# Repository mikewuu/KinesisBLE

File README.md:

# Wireless Kinesis Advantage BLE (Bluetooth Low Energy)

Turns the [Kinesis Advantage Keyboard](https://www.kinesis-ergo.com/shop/advantage2/) keyboard into a wireless BLE keyboard with a few extra features. Built with Adafruit's nRF52 Feather Arduino boards.

For instructions, see the **[wiki](https://github.com/sysdevmike/KinesisBLE/wiki)**. For more details on the build check out the **[project](https://hackaday.io/project/161578-wireless-ble-kinesis-advantage-custom-controller)**.

## Many thanks to

- [Yin Zhong](https://summivox.wordpress.com/2016/06/03/keyboard-matrix-scanning-and-debouncing/) - Explains a better way to handle debouncing.
- [Stapelberg](https://michael.stapelberg.ch/posts/2018-04-17-kinx-keyboard-controller/) - Double mention as I ported his debouncing used in his KinX controller to Matt's firmware.
- [Matt Vilim](https://github.com/mattvilim/FeatherCtrl) - New firmware is a fork of his FeatherCtrl project.
- [Adafruit](https://www.adafruit.com/product/3406) - Great documentation, libs and support.
- [afriggeri](https://github.com/afriggeri/kb) - The original firmware borrowed heavily from his [Blanck Keyboard](https://medium.com/@friggeri/the-blanck-keyboard-24afe12e81a) project.
- [Stapelberg](https://michael.stapelberg.de/posts/2013-03-21-kinesis_custom_controller/) - Michael Stapelberg's custom controller inspired this project. His PCB routing was inspirational.
- [Humble Hacker](http://humblehacker.com/blog/20100720/hacking-the-kinesis-contoured-keyboard/) - Detailed write-up helped me understand the keyboard matrix.
- [PCBgogo](http://www.pcbgogo.com) - All the boards were made by these guys. Fast turn-around.

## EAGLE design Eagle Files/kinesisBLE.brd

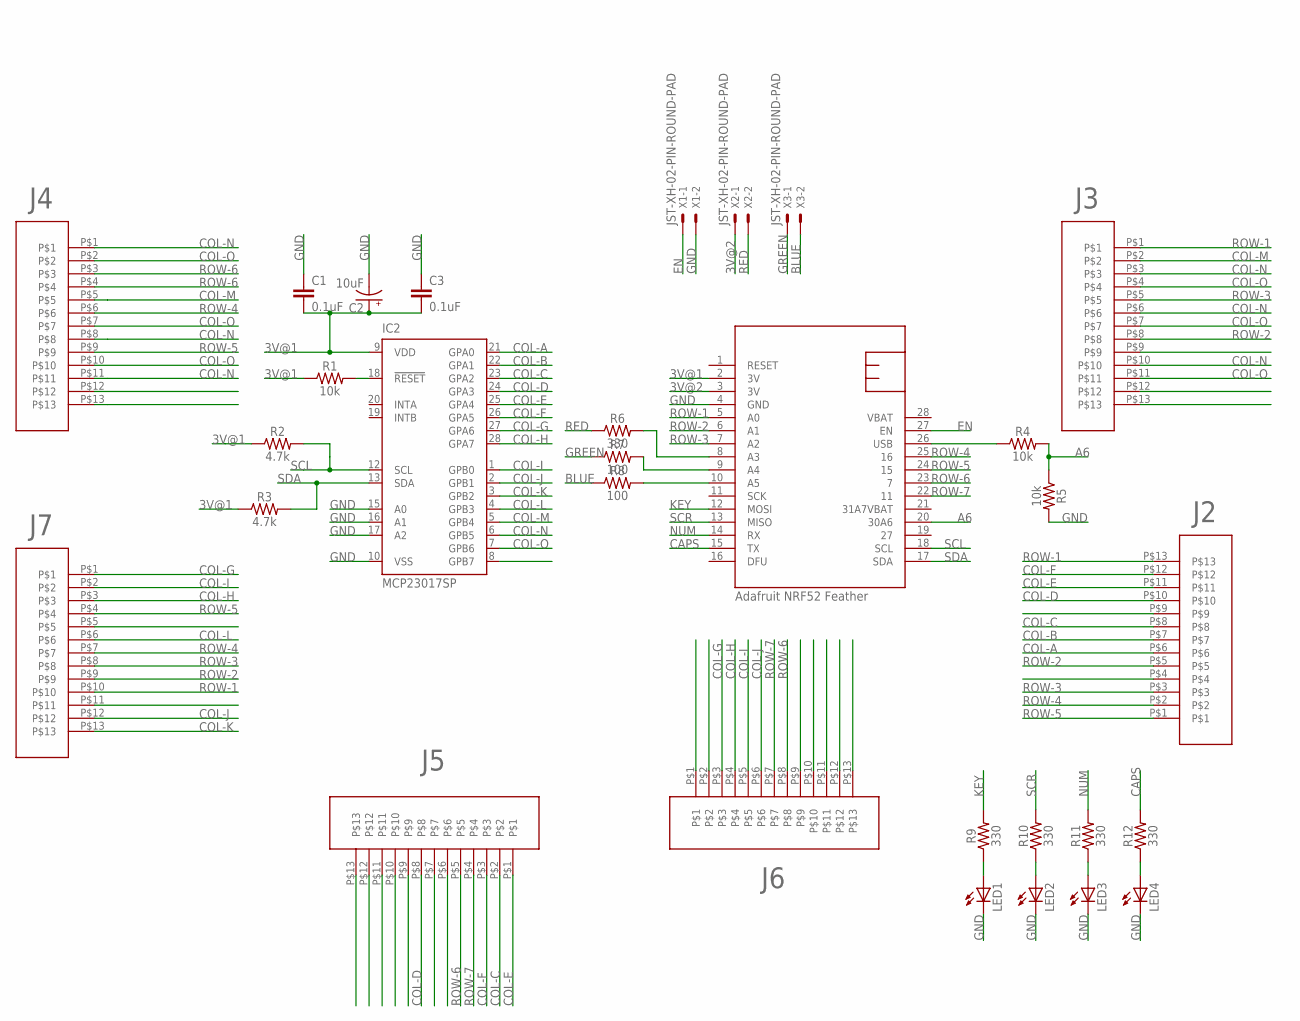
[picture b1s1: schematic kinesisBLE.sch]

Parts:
C1, C3: 0.1uF; CAP-PTH-SMALL-KIT
C2: 10uF; CPOL-RADIAL-2.5MM-5MM
IC2: MCP23017SP; DIL28-3
LED1, LED2, LED3, LED4: LED3MM
R1, R4, R5: 10k; AXIAL-0.3
R2, R3: 4.7k; AXIAL-0.3
R6, R9, R10, R11, R12: 330; AXIAL-0.3
R7, R8: 100; AXIAL-0.3
U$1: NRF52FEATHER
U$2, U$3, U$4, U$5, U$6, U$7: TOPLINKS_STAPELBERG
X1, X2, X3: JST-XH-02-PIN-ROUND-PAD; JST-XH-02-PACKAGE-ROUND-PAD

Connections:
3V@1: C1.2, C2.1 (+), C3.2, IC2.9 (VDD), R1.P$1 (1), R2.P$1 (1), R3.P$1 (1), U$1.2 (3V)
3V@2: U$1.3 (3V), X2.1
A6: R4.P$2 (2), R5.P$1 (1), U$1.20 (30A6)
BLUE: R8.P$1 (1), X3.2
CAPS: R12.P$2 (2), U$1.15 (TX)
COL-A: IC2.21 (GPA0), U$5.P$6
COL-B: IC2.22 (GPA1), U$5.P$7
COL-C: IC2.23 (GPA2), U$5.P$8, U$6.P$2
COL-D: IC2.24 (GPA3), U$5.P$10, U$6.P$8
COL-E: IC2.25 (GPA4), U$5.P$11, U$6.P$1
COL-F: IC2.26 (GPA5), U$5.P$12, U$6.P$3
COL-G: IC2.27 (GPA6), U$4.P$1, U$7.P$3
COL-H: IC2.28 (GPA7), U$4.P$3, U$7.P$4
COL-I: IC2.1 (GPB0), U$4.P$2, U$7.P$5
COL-J: IC2.2 (GPB1), U$4.P$12, U$7.P$6
COL-K: IC2.3 (GPB2), U$4.P$13
COL-L: IC2.4 (GPB3), U$4.P$6
COL-M: IC2.5 (GPB4), U$2.P$5, U$3.P$2
COL-N: IC2.6 (GPB5), U$2.P$1, U$2.P$8, U$2.P$11, U$3.P$3, U$3.P$6, U$3.P$10
COL-O: IC2.7 (GPB6), U$2.P$2, U$2.P$7, U$2.P$10, U$3.P$4, U$3.P$7, U$3.P$11
EN: U$1.27 (EN), X1.1
GND: C1.1, C2.2 (-), C3.1, IC2.10 (VSS), IC2.15 (A0), IC2.16 (A1), IC2.17 (A2), LED1.K (C), LED2.K (C), LED3.K (C), LED4.K (C), R5.P$2 (2), U$1.4 (GND), X1.2
GREEN: R7.P$1 (1), X3.1
KEY: R9.P$2 (2), U$1.12 (MOSI)
unnamed: LED1.A, R9.P$1 (1)
unnamed: IC2.18 (!RESET), R1.P$2 (2)
unnamed: R4.P$1 (1), U$1.26 (USB)
unnamed: R6.P$2 (2), U$1.8 (A3)
unnamed: R7.P$2 (2), U$1.9 (A4)
unnamed: R8.P$2 (2), U$1.10 (A5)
unnamed: LED2.A, R10.P$1 (1)
unnamed: LED3.A, R11.P$1 (1)
unnamed: LED4.A, R12.P$1 (1)
NUM: R11.P$2 (2), U$1.14 (RX)
RED: R6.P$1 (1), X2.2
ROW-1: U$1.5 (A0), U$3.P$1, U$4.P$10, U$5.P$13
ROW-2: U$1.6 (A1), U$3.P$8, U$4.P$9, U$5.P$5
ROW-3: U$1.7 (A2), U$3.P$5, U$4.P$8, U$5.P$3
ROW-4: U$1.25 (16), U$2.P$6, U$4.P$7, U$5.P$2
ROW-5: U$1.24 (15), U$2.P$9, U$4.P$4, U$5.P$1
ROW-6: U$1.23 (7), U$2.P$3, U$2.P$4, U$6.P$5, U$7.P$8
ROW-7: U$1.22 (11), U$6.P$4, U$7.P$7
SCL: IC2.12 (SCL), R2.P$2 (2), U$1.18 (SCL)
SCR: R10.P$2 (2), U$1.13 (MISO)
SDA: IC2.13 (SDA), R3.P$2 (2), U$1.17 (SDA)
VBAT: U$1.28 (VBAT)

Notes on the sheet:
Adafruit NRF52 Feather

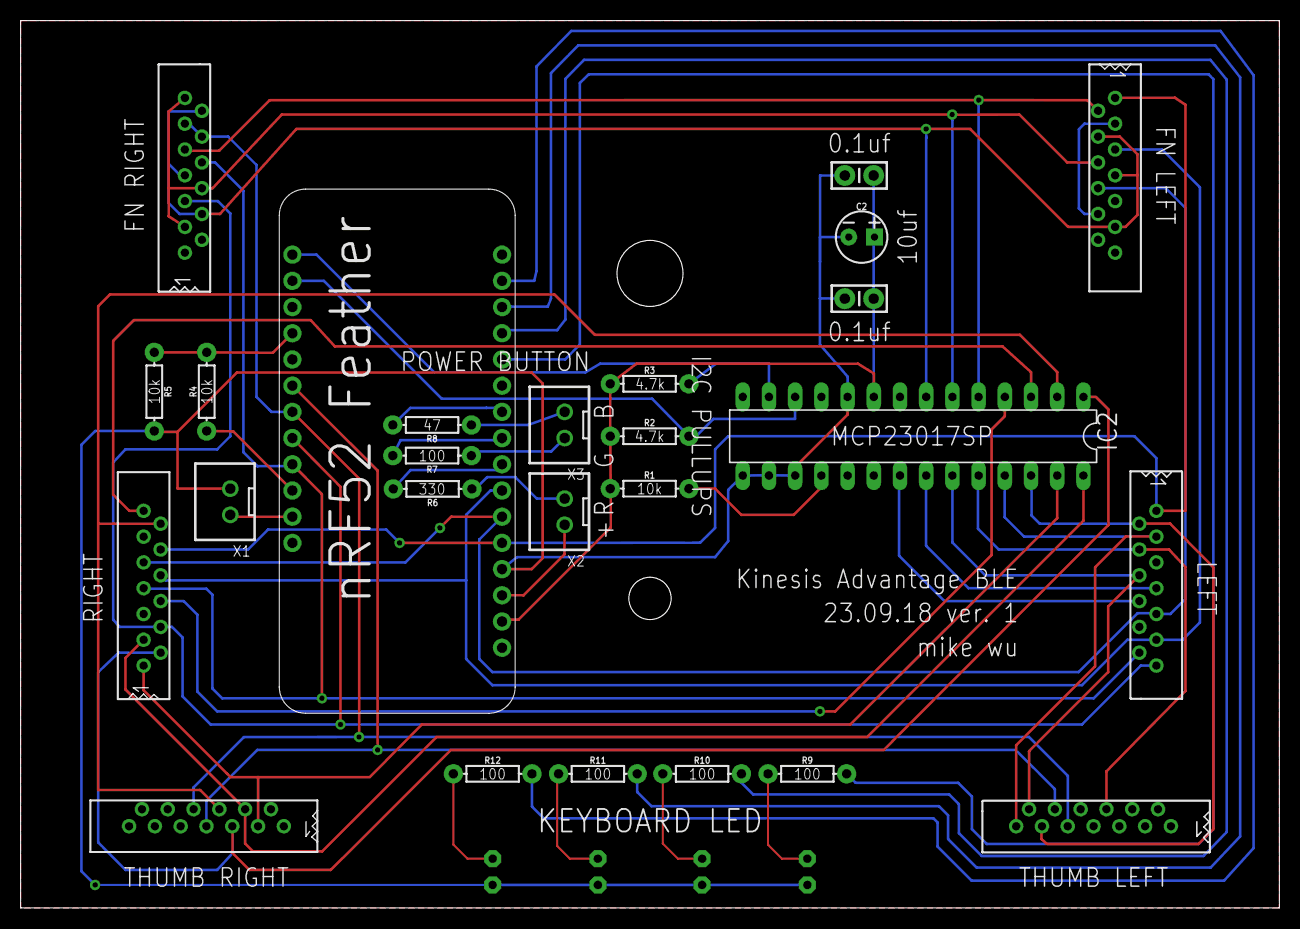
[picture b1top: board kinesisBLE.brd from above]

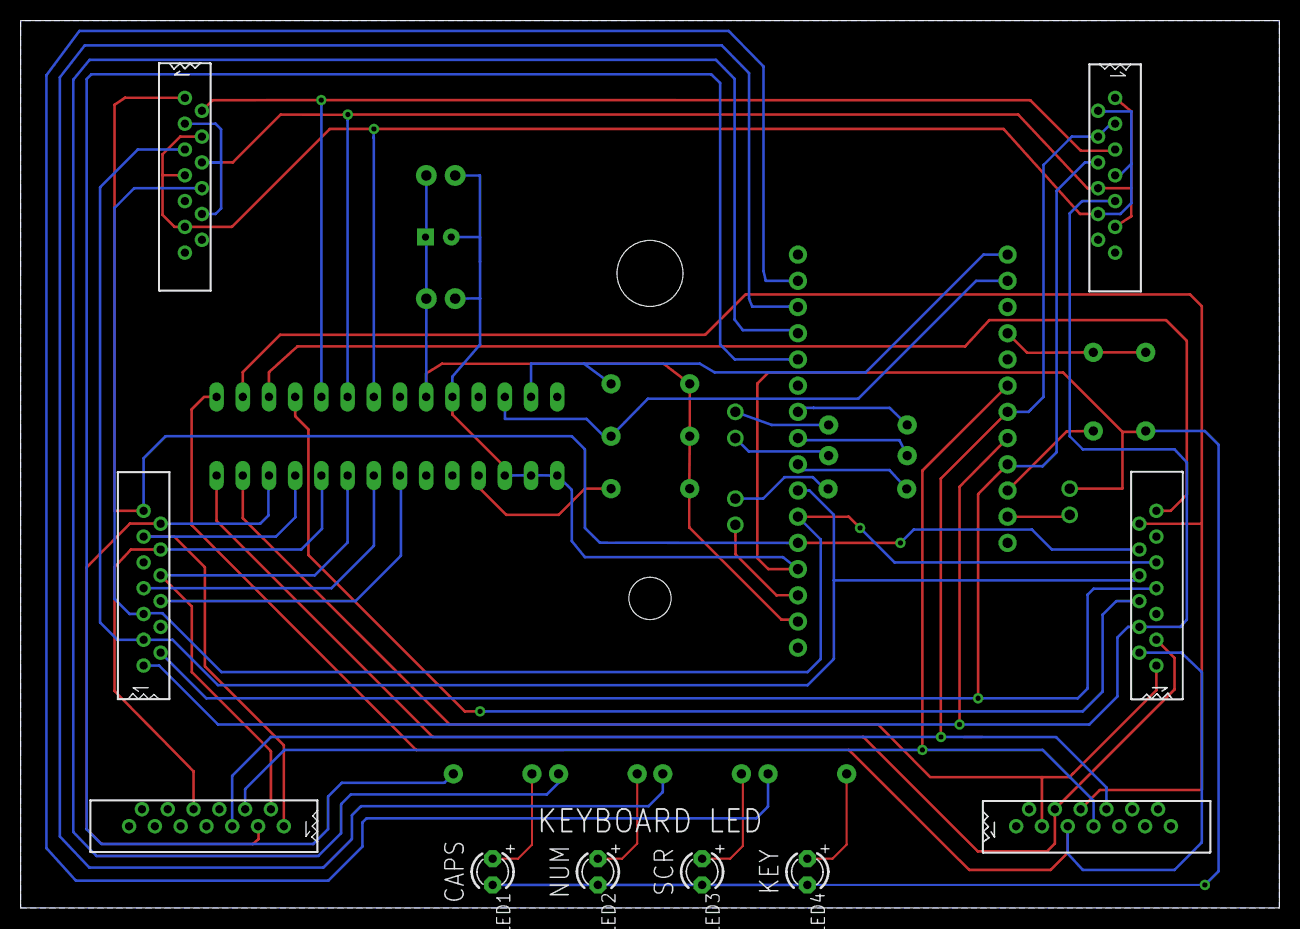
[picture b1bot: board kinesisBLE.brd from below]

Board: 2 copper layers, 122.0 x 86.0 mm, 30 parts (7 on the bottom side), 45 nets.

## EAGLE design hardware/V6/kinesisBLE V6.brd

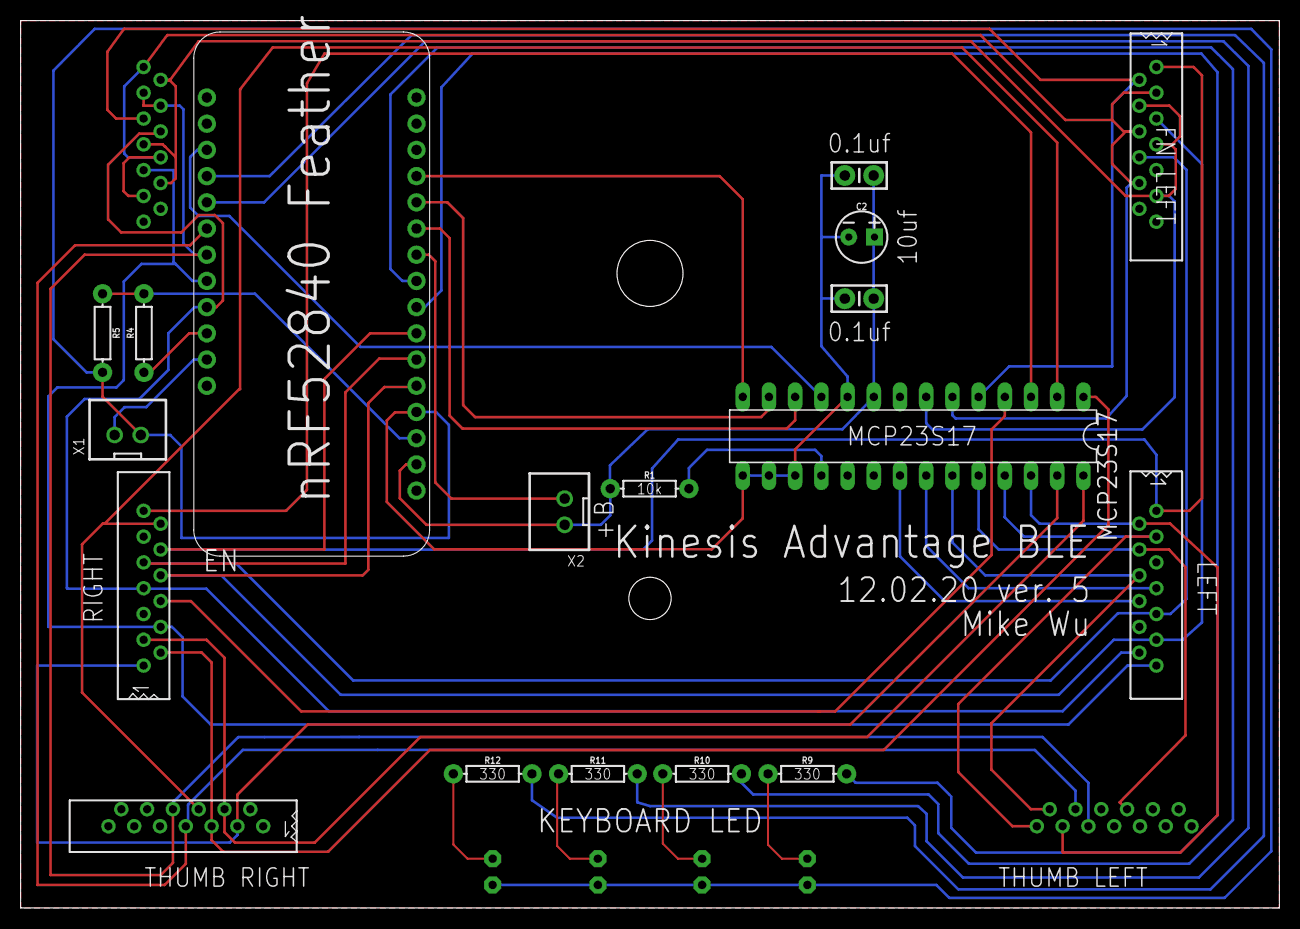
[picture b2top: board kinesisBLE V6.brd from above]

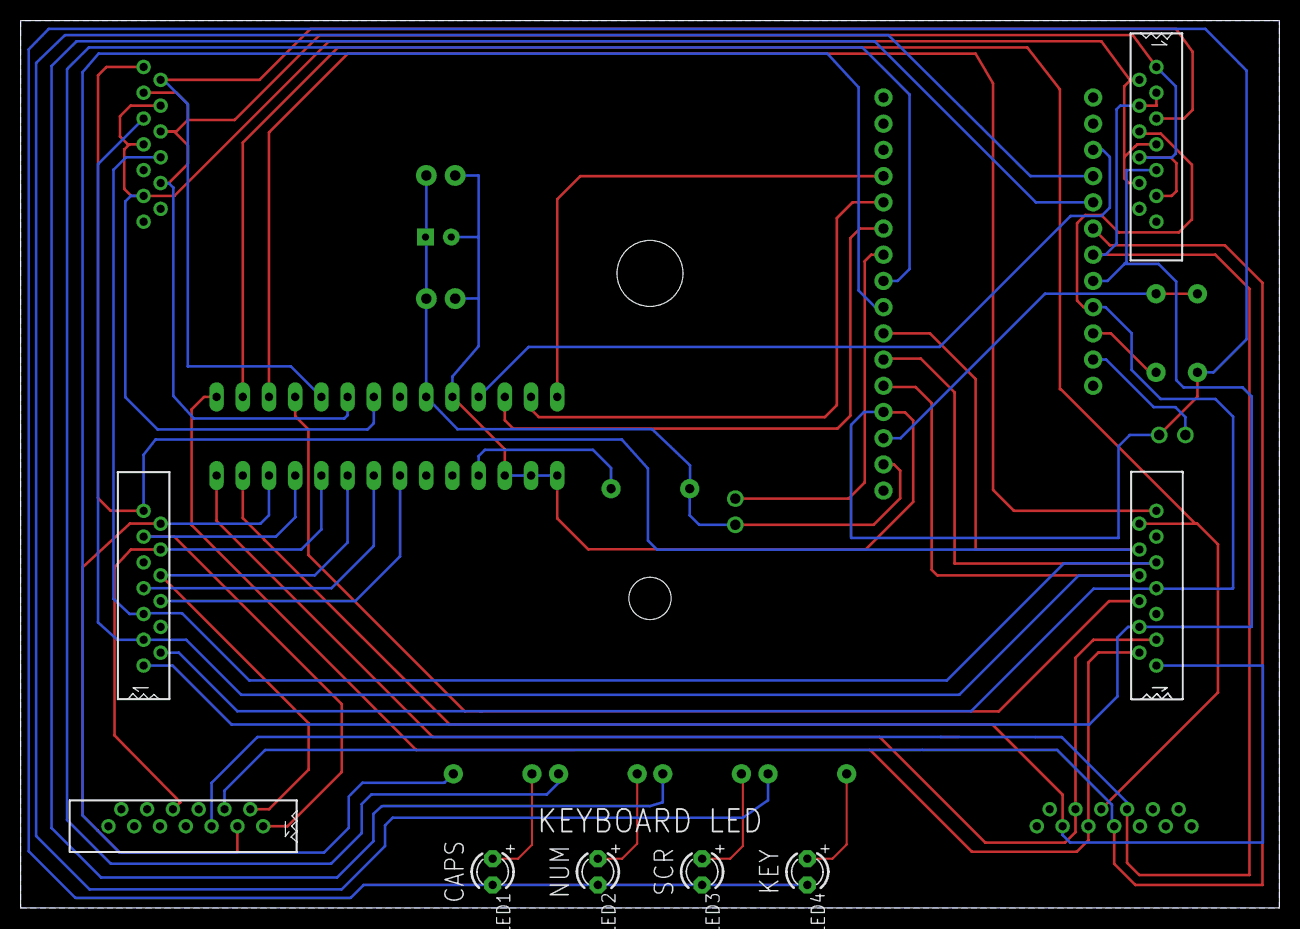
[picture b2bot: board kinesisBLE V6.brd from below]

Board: 2 copper layers, 122.0 x 86.0 mm, 24 parts (7 on the bottom side), 41 nets.

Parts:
C1, C3: 0.1uF; CAP-PTH-SMALL-KIT
C2: 10uF; CPOL-RADIAL-2.5MM-5MM
LED1, LED2, LED3, LED4: LED3MM
MCP23S17: MCP23S17SP; DIL28-3
R1, R4, R5: 10k; AXIAL-0.3
R9, R10, R11, R12: 330; AXIAL-0.3
U$1: NRF52FEATHER
U$2, U$3, U$4, U$5, U$6, U$7: TOPLINKS_STAPELBERG
X1, X2: JST-XH-02-PIN-ROUND-PAD; JST-XH-02-PACKAGE-ROUND-PAD

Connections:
3V@1: C1.2, C2.1, C3.2, MCP23S17.9, R1.P$1, U$1.2, X2.1
AREF: R4.P$2, R5.P$1, U$1.3
BLUE: U$1.10, X2.2
CAPS: R9.P$2, U$1.8
COL-A: MCP23S17.21, U$5.P$6
COL-B: MCP23S17.22, U$5.P$7
COL-C: MCP23S17.23, U$5.P$8, U$6.P$2
COL-D: MCP23S17.24, U$5.P$10, U$6.P$8
COL-E: MCP23S17.25, U$5.P$11, U$6.P$1
COL-F: MCP23S17.26, U$5.P$12, U$6.P$3
COL-G: MCP23S17.27, U$4.P$1, U$7.P$3
COL-H: MCP23S17.28, U$4.P$3, U$7.P$4
COL-I: MCP23S17.1, U$4.P$2, U$7.P$5
COL-J: MCP23S17.2, U$4.P$12, U$7.P$6
COL-K: MCP23S17.3, U$4.P$13
COL-L: MCP23S17.4, U$4.P$6
COL-M: MCP23S17.5, U$2.P$5, U$3.P$2
COL-N: MCP23S17.6, U$2.P$1, U$2.P$8, U$2.P$11, U$3.P$3, U$3.P$6, U$3.P$10
COL-O: MCP23S17.7, U$2.P$2, U$2.P$7, U$2.P$10, U$3.P$4, U$3.P$7, U$3.P$11
EN: U$1.27, X1.1
GND: C1.1, C2.2, C3.1, LED1.K, LED2.K, LED3.K, LED4.K, MCP23S17.10, MCP23S17.15, MCP23S17.16, MCP23S17.17, R5.P$2, U$1.4, X1.2
KEY: R12.P$2, U$1.20
MISO: MCP23S17.14, U$1.13
MOSI: MCP23S17.13, U$1.12
unnamed: LED1.A, R9.P$1
unnamed: MCP23S17.18, R1.P$2
unnamed: R4.P$1, U$1.26
unnamed: LED2.A, R10.P$1
unnamed: LED3.A, R11.P$1
unnamed: LED4.A, R12.P$1
NUM: R10.P$2, U$1.9
ROW-1: U$1.7, U$3.P$1, U$4.P$10, U$5.P$13
ROW-2: U$1.6, U$3.P$8, U$4.P$9, U$5.P$5
ROW-3: U$1.5, U$3.P$5, U$4.P$8, U$5.P$3
ROW-4: U$1.25, U$2.P$6, U$4.P$7, U$5.P$2
ROW-5: U$1.24, U$2.P$9, U$4.P$4, U$5.P$1
ROW-6: U$1.23, U$2.P$3, U$2.P$4, U$6.P$5, U$7.P$8
ROW-7: U$1.22, U$6.P$4, U$7.P$7
SCK: MCP23S17.12, U$1.11
SCR: R11.P$2, U$1.21
SS: MCP23S17.11, U$1.19

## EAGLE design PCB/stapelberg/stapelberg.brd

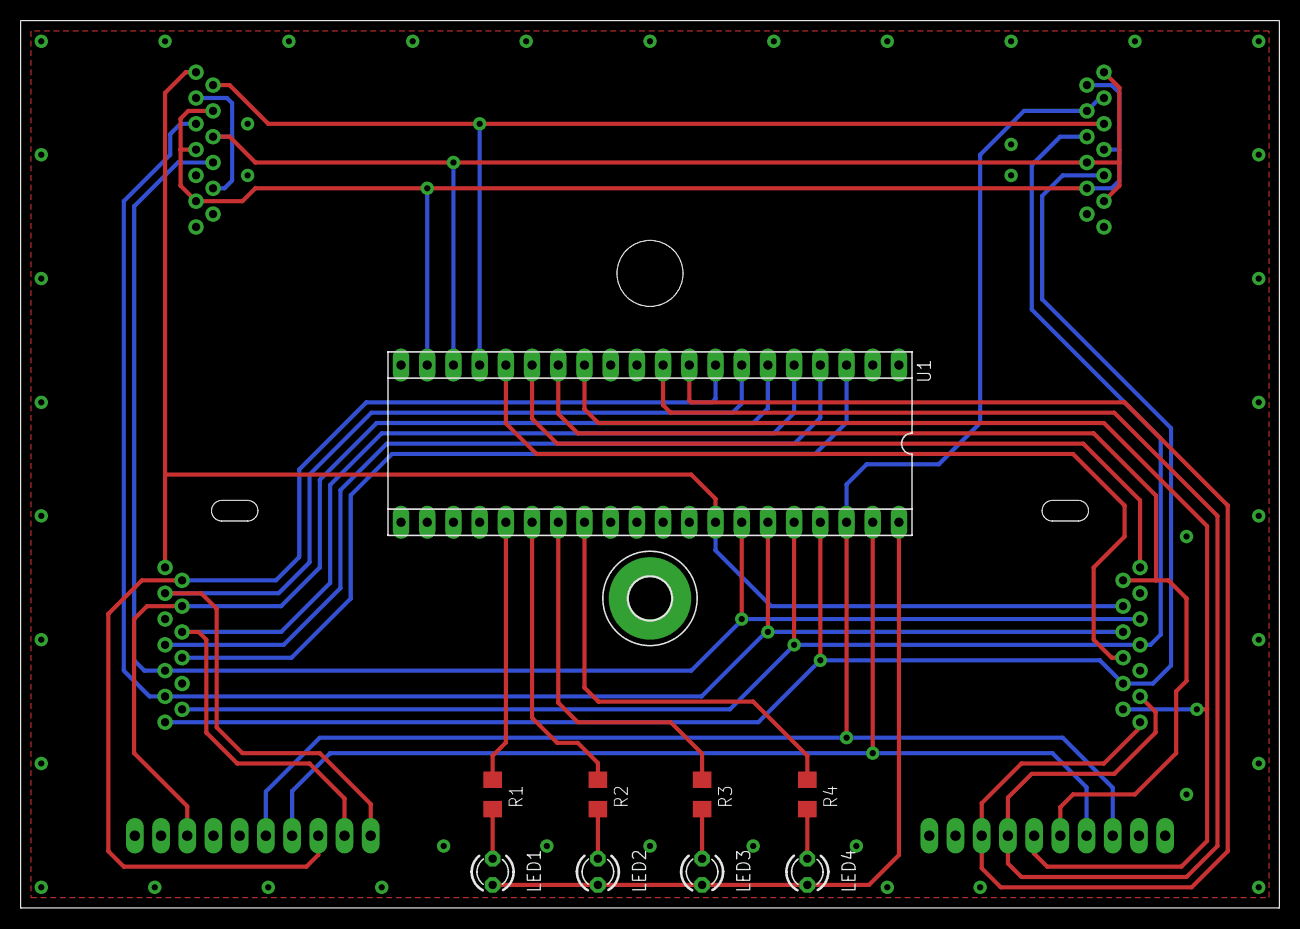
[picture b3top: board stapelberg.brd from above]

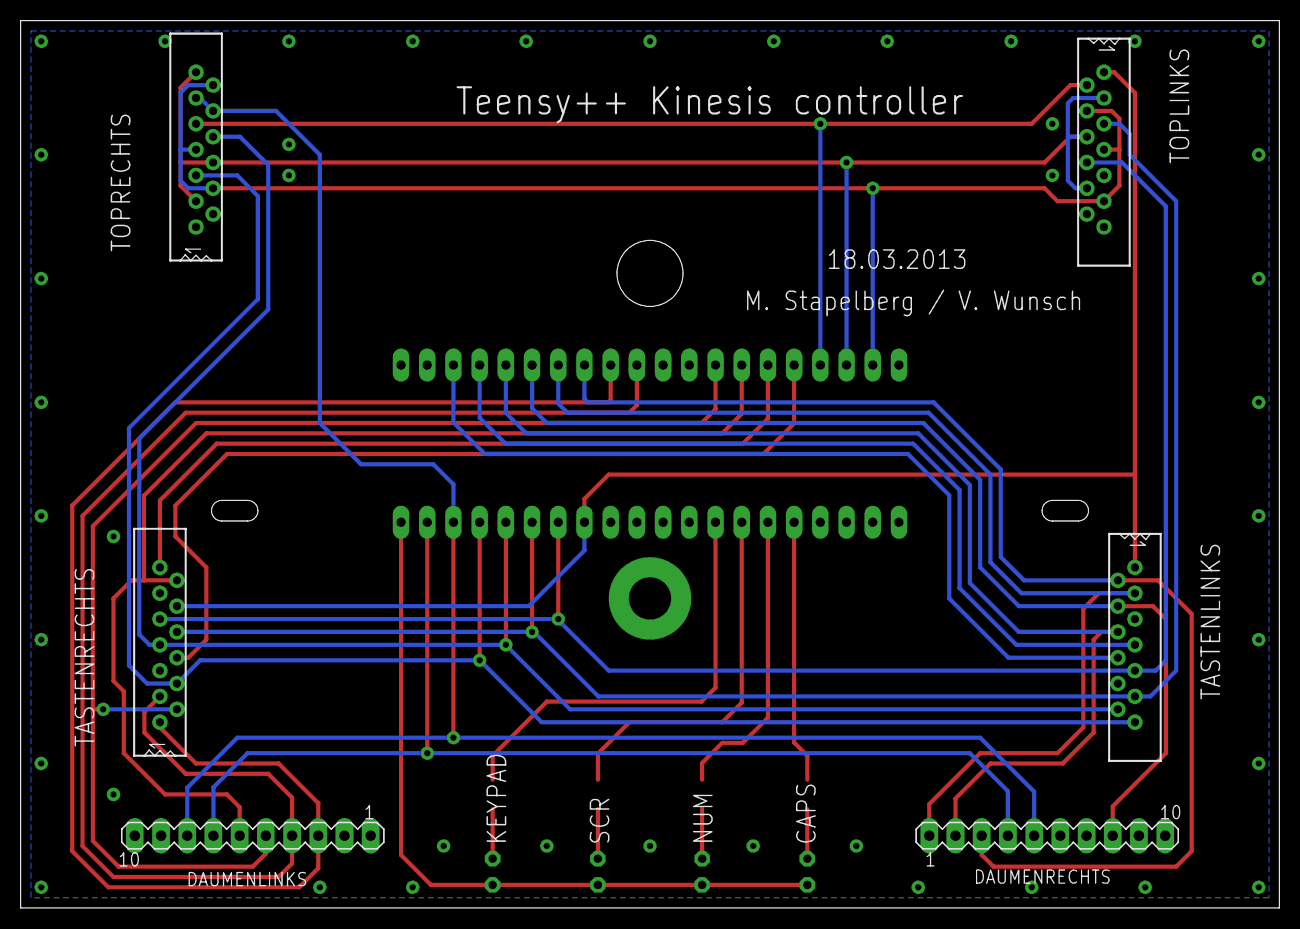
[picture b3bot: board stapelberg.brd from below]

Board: 2 copper layers, 122.0 x 86.0 mm, 16 parts (6 on the bottom side), 31 nets.

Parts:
DAUMENLINKS: MA10-1
DAUMENRECHTS: MA10-1
H1: MOUNT-PAD-ROUND4.1; 4,1-PAD
LED1, LED2, LED3, LED4: LED3MM
R1, R2, R3, R4: R1206
TASTENLINKS: 39-53-2355; 39-53-2135
TASTENRECHTS: 39-53-2355; 39-53-2135
TOPLINKS: 39-53-2355; 39-53-2135
TOPRECHTS: 39-53-2355; 39-53-2135
U1: C-TEENSY++; TEENSY++

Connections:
B0: TASTENLINKS.P$1, TASTENRECHTS.P$10, TOPLINKS.P$1, U1.B0
B1: TASTENLINKS.P$9, TASTENRECHTS.P$9, TOPLINKS.P$8, U1.B1
B2: TASTENLINKS.P$11, TASTENRECHTS.P$8, TOPLINKS.P$5, U1.B2
B3: TASTENLINKS.P$12, TASTENRECHTS.P$7, TOPRECHTS.P$8, U1.B3
B4: TASTENLINKS.P$13, TASTENRECHTS.P$4, TOPRECHTS.P$5, U1.B4
B5: DAUMENLINKS.8, DAUMENRECHTS.5, TOPRECHTS.P$10, TOPRECHTS.P$11, U1.B5
B6: DAUMENLINKS.7, DAUMENRECHTS.4, U1.B6
C0: DAUMENLINKS.5, TASTENRECHTS.P$2, U1.C0
C1: DAUMENLINKS.6, TASTENRECHTS.P$12, U1.C1
C2: TASTENRECHTS.P$13, U1.C2
C3: TASTENRECHTS.P$6, U1.C3
C4: TOPLINKS.P$2, TOPRECHTS.P$9, U1.C4
C5: TOPLINKS.P$3, TOPLINKS.P$6, TOPLINKS.P$10, TOPRECHTS.P$3, TOPRECHTS.P$6, TOPRECHTS.P$13, U1.C5
C6: TOPLINKS.P$4, TOPLINKS.P$7, TOPLINKS.P$11, TOPRECHTS.P$4, TOPRECHTS.P$7, TOPRECHTS.P$12, U1.C6
D0: TASTENLINKS.P$8, U1.D0
D1: TASTENLINKS.P$7, U1.D1
D2: DAUMENRECHTS.2, TASTENLINKS.P$6, U1.D2
D3: DAUMENRECHTS.8, TASTENLINKS.P$4, U1.D3
D4: DAUMENRECHTS.1, TASTENLINKS.P$3, U1.D4
D5: DAUMENRECHTS.3, TASTENLINKS.P$2, U1.D5
D6: DAUMENLINKS.3, TASTENRECHTS.P$1, U1.D6
D7: DAUMENLINKS.4, TASTENRECHTS.P$3, U1.D7
unnamed: R1.2, U1.F3
unnamed: R2.2, U1.F2
unnamed: R3.2, U1.F1
unnamed: R4.2, U1.F0
unnamed: LED1.A, LED2.A, LED3.A, LED4.A, U1.+5V
unnamed: LED4.K, R4.1
unnamed: LED3.K, R3.1
unnamed: LED2.K, R2.1
unnamed: LED1.K, R1.1

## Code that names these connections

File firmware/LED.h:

#ifndef LED_H
#define LED_H

#include <bluefruit.h>

class LED {
  public:
  
    const static uint8_t CAPS_PIN = A3;
    const static uint8_t NUM_PIN = A4;
    const static uint8_t SCR_PIN = 9;
    const static uint8_t KEY_PIN = 6; 
    
    LED(void);
    void begin(void);
    void numLEDsOnForDuration(int num, unsigned long duration);
    void process(void);
    void offAll(void);
    void flashWithSpeed(bool speed);
    void stopFlashing(void);
    
  private:

    const uint8_t POWER_BUTTON_PIN = A5;    
    const uint8_t powerButtonBrightness = 175;
    bool shouldTurnOffAfterDuration;
    unsigned long onTime;
    unsigned long onDuration;
    bool isFlashing;
    bool flashingLedOn;
    bool flashSpeed;
    unsigned long lastFlashTime;
    unsigned long slowFlashGap;
    unsigned long fastFlashGap;
    
    void setLED(int pin, bool state);
    void setAllLEDs(bool state);
    void powerButtonOn(void);
    void powerButtonOff(void);
    void LEDsOff(void);
};


#endif

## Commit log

2016-11-20 Importing all the code
2016-11-20 Use waitForOK instead of a delay
2016-11-28 Rebuild because Bluefruit died, switched a few pins around
2016-12-06 Prevent stuck modifiers
2016-12-06 Remap MUTE
2016-12-06 Set AT+GAPINTERVALS=10,30,,
2017-03-04 Lower BLE power level
2017-05-12 bunch of changes
2018-09-23 Include stapelberg board files
2018-09-24 Remove reading battery ADC and added comments
2018-09-24 switched Q and A keycodes
2018-09-24 Set Kinesis key matrix
2018-09-24 Rename to KinesisBLE
2018-09-24 Write key changes to serial
2018-09-24 Set bluetooth settings from current nRF52 setup
2018-09-27 Switch columns and rows. Detects key presses according to Humble Hacker matrix.
2018-09-28 First complete working version. No LEDs.
2018-09-28 Battery indicator LEDs
2018-09-28 Power Button LED
2018-09-29 Fix measure battery every 10 seconds
2018-10-01 Test power-saving code
2018-10-01 Battery LED off timer. Shutdown (deep-sleep) after inactivity.
2018-10-01 readme
2018-10-01 Decrease Blue power button led to 80/255 = 1.9mA. Remove built-in LED sleep indicator that was used for testing.
2018-10-01 Add Eagle files
2018-10-01 Move example code into directory
2018-10-02 Debounce once as MCP takes 20-30ms to go through one loop anyway. Fix use correct pins for LEDS and power button.
2018-10-03 Change LED pins from Serial. Fix not waking up from shutdown.
2018-10-03 Add charging animation. Make power button more orange when charging.
2018-10-03 Fix charging animation to stop at actual level when unplugged.
2018-10-03 V2 Board. Re-route LEDs to not use Serial pins.
2018-10-04 Check if full from battery mv instead of reading USB.
2018-10-04 Keyboard Layers.
2018-10-04 Go back to measuring USB voltage with smoothing
2018-10-04 Fix min usb mv
2018-10-10 Increase Power LED blue power to 125 (2mA). More keymap mappings for second layer.
2018-10-10 Raised layer keymaps: brackets and quotes.
2018-10-16 Remove Serial.begin for power saving
2018-10-18 Set up with SPI and power saving
2018-10-19 Use v3 board pins
2018-10-22 v3 board files
2018-10-24 Turned power led back on
2018-10-24 change delay to 14
2018-10-28 V4 - Took LED(s) off TX/RX. Blue button only (lost RGB) to fix CP2104 battery drain.
2018-10-28 Fix: Skipping key-presses at 14ms delay. Reduced delay to 7ms.
2018-10-30 Removed all power / battery features due to ADC current leak
2018-10-30 Fixed current drain issue due to FPU
2018-10-30 Cleanup
2018-10-31 Reduce battery indicator LED on time from 5mins to 30 seconds
2018-11-04 bug fix: hitting K_NONE 0x0000 key crashed keyboard.
2018-11-06 turn off battery led after 30 seconds
2018-11-16 lowered battery led brightness and increased duration to 3 mins.
2018-11-16 bug fix: led didn't blink when charging after switching to analogWrite.
2018-11-17 indicate battery level on progm key
2018-11-17 keyp to show battery level and progm to shutdown
2018-11-18 Moved sys configs into config.h
2018-11-18 fixed indentation
2018-11-18 Featuer: Rest Timer
2018-11-19 cleaned up rest_timer code
2018-11-19 clean up loop and add handle_command method
2018-11-19 changed rest timer settings
2018-11-19 manually enter break mode
2018-11-19 set work interval back to a more reasonable 20mins
2018-11-20 set shutdown to new key code K_RSTD
2019-01-27 remove typo
2019-01-28 add clear bond combo
2019-01-28 flash led to indicate cleared
2019-02-11 cleanup setup. remove redundant comments. set work afk timer to 20mins
2019-03-18 Increase USB_FULL_MIN_MV to 4990
2019-04-22 Remove generated eagle files.
2019-04-22 BREAKING CHANGE - Revert to v3 pin numbers for use with nRF8240. Make sure you are building v3 (not v4!) board from this point forward.
2019-04-28 Modify to work with 840.
2019-04-28 Go back to v4 pins.
2019-04-28 Comments
2019-04-28 more comments.
2019-05-01 Add V4 gerbers.
2019-05-13 Remove keyboard chatter - decrease delay, and increase debounce loops.
2019-05-13 Increase delay to 4ms
2019-05-13 Turn off debug
2019-05-15 Decrease delay to 2
2019-05-15 Use unsigned long for timestamps.
2019-06-09 Use new firmare.
2019-06-09 Change name to KinesisBLE.
2019-06-19 Increase debounce time to 10ms.
2019-06-19 Increase bluetooth power.
2019-06-19 Go back to nrf52 0.8.6 because analogWrite would turn on bluetooth LED on 0.9.2.
2019-07-29 Set capslock back to capslock instead of esc.
2019-07-30 Implement Power and LED.
2019-07-30 Show battery level on power on.
2019-08-01 Move led logic into LED class.
2019-08-01 Add LED flash.
2019-08-01 Setup rest classes.
2019-08-01 Implement Pomodoro timer.
2019-08-01 Cleanup debug.
2019-08-01 Use pomodoro times.
2019-09-06 Bind caps to esc. And program to hyper (f18, implemented in hammerspoon)
2019-12-11 Bind Delete to hyper key
2020-02-14 V5 Board for nRF52840
2020-02-14 Switch to nRF52840 v5 board pins
2020-02-25 send report over usb
2020-02-26 Works! -- Set blue/power button pin to A5
2020-02-26 Fix sending double key reports.
2020-02-26 Allow opt-in rest timer from config
2020-02-26 Send report directly using usb_hid.sendReport instead of splitting keycodes and modifiers.
2020-02-26 Prevent deep-sleep when connected to USB
2020-02-27 Remove .DS_Store from git
2020-02-27 Clean up hardware folder
2020-02-29 Clean up HID report. Update to use 840 VBAT_COMP.
2020-03-02 Set USB Product name, and manufacturer.
2020-03-02 Set model from BLE to Bluetooth
2020-03-10 Fix REST_TIMER not being set
2020-06-17 Disable rest timer by default
2021-02-04 Add v6 board
2021-03-21 Add v6 gerbers

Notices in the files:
parts and their libraries:
SparkFun-Resistors: Licensing: Creative Commons ShareAlike 4.0 International - https://creativecommons.org/licenses/by-sa/4.0
